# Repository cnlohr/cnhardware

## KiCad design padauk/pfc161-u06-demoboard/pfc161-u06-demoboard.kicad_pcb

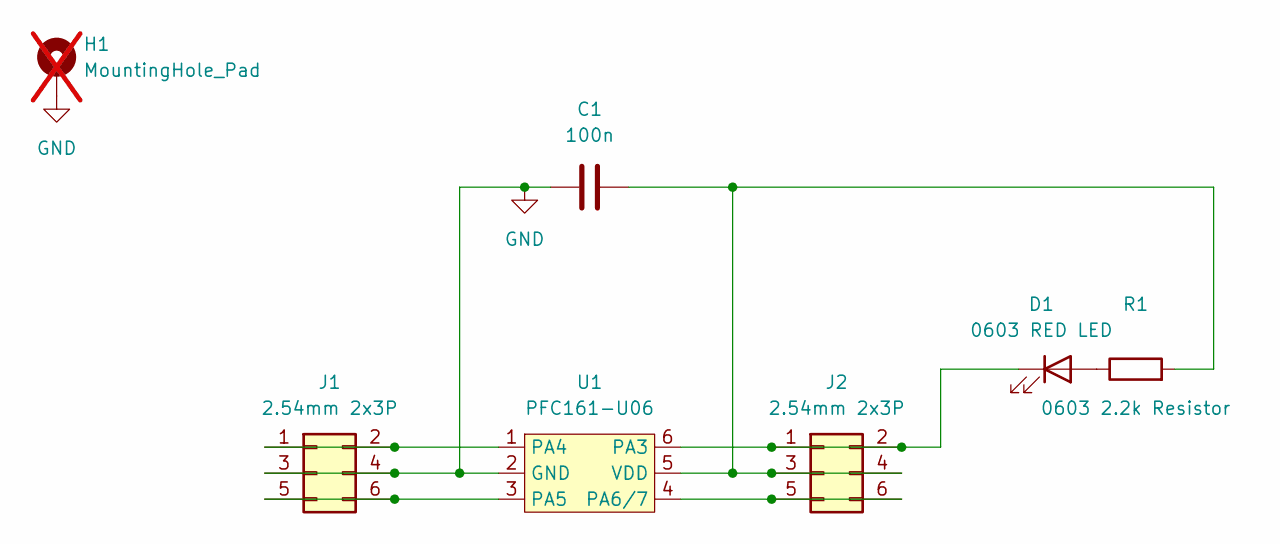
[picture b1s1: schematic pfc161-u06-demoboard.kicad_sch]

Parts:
C1: 100n; C_0402_1005Metric; LCSC C1525
D1: 0603 RED LED; LED_0603_1608Metric; LCSC C2286
H1: MountingHole_Pad; MountingHole_3.2mm_M3_Pad; not fitted
J1, J2: 2.54mm 2x3P; PinHeader_2x03_P2.54mm_Vertical; LCSC C65114
R1: 0603 2.2k Resistor; R_0603_1608Metric; LCSC C2907137
U1: PFC161-U06; SOT-23-6; LCSC C2909526

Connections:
GND: C1.1, H1.1, J1.3, J1.4, U1.2 (GND)
unnamed: D1.2 (A), R1.1
unnamed: D1.1 (K), J2.1, J2.2, U1.6 (PA3)
unnamed: J1.1, J1.2, U1.1 (PA4)
unnamed: J1.5, J1.6, U1.3 (PA5)
unnamed: C1.2, J2.3, J2.4, R1.2, U1.5 (VDD)
unnamed: J2.5, J2.6, U1.4 (PA6/7)

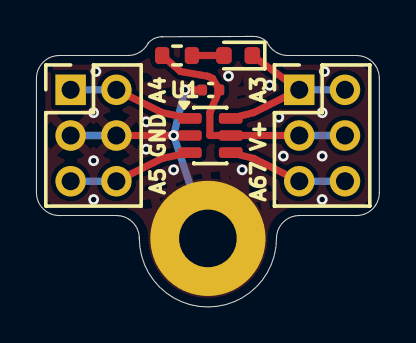
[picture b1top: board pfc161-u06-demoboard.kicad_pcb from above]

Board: 2 copper layers, 19.0 x 15.0 mm, 7 parts (0 on the bottom side), 7 nets.

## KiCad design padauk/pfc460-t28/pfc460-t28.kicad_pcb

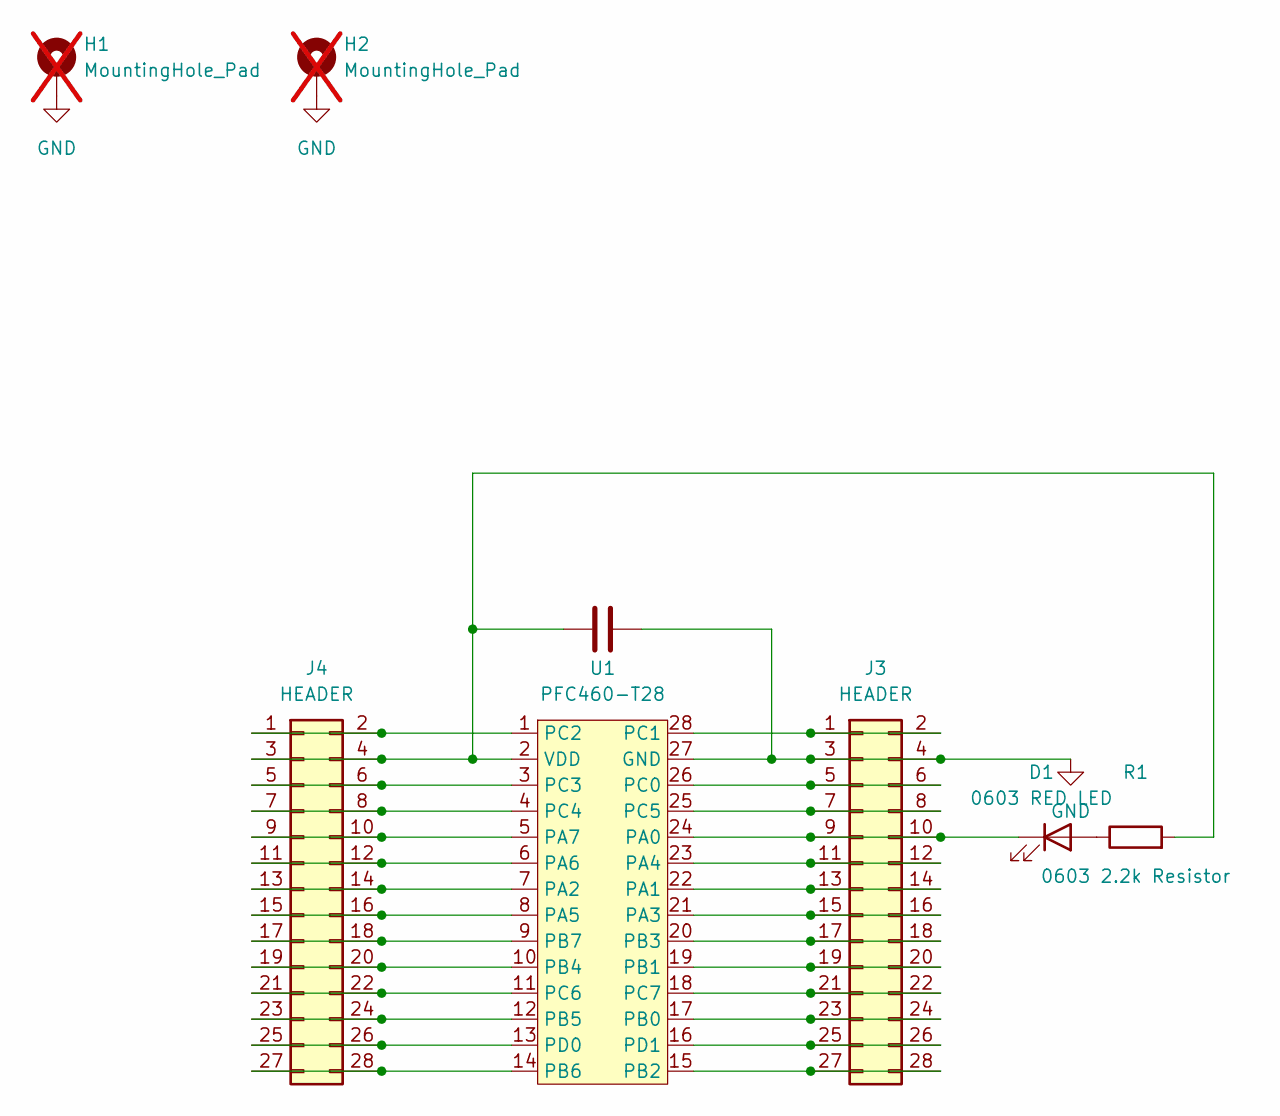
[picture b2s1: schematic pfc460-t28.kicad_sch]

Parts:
C2: 100n; C_0402_1005Metric; LCSC C1525
D1: 0603 RED LED; LED_0603_1608Metric; LCSC C2286
H1, H2: MountingHole_Pad; MountingHole_3.2mm_M3_Pad; not fitted
J3, J4: HEADER; PinHeader_2x14_P2.54mm_Vertical; LCSC C41376105
R1: 0603 2.2k Resistor; R_0603_1608Metric; LCSC C2907137
U1: PFC460-T28; TSSOP-28_4.4x9.7mm_P0.65mm; LCSC C22365215

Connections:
GND: C2.2, H1.1, H2.1, J3.3, J3.4, U1.27 (GND)
unnamed: D1.2 (A), R1.1
unnamed: D1.1 (K), J3.9, J3.10, U1.24 (PA0)
unnamed: J3.1, J3.2, U1.28 (PC1)
unnamed: J3.5, J3.6, U1.26 (PC0)
unnamed: J3.7, J3.8, U1.25 (PC5)
unnamed: J3.11, J3.12, U1.23 (PA4)
unnamed: J3.13, J3.14, U1.22 (PA1)
unnamed: J3.15, J3.16, U1.21 (PA3)
unnamed: J3.17, J3.18, U1.20 (PB3)
unnamed: J3.19, J3.20, U1.19 (PB1)
unnamed: J3.21, J3.22, U1.18 (PC7)
unnamed: J3.23, J3.24, U1.17 (PB0)
unnamed: J3.25, J3.26, U1.16 (PD1)
unnamed: J3.27, J3.28, U1.15 (PB2)
unnamed: J4.1, J4.2, U1.1 (PC2)
unnamed: C2.1, J4.3, J4.4, R1.2, U1.2 (VDD)
unnamed: J4.5, J4.6, U1.3 (PC3)
unnamed: J4.7, J4.8, U1.4 (PC4)
unnamed: J4.9, J4.10, U1.5 (PA7)
unnamed: J4.11, J4.12, U1.6 (PA6)
unnamed: J4.13, J4.14, U1.7 (PA2)
unnamed: J4.15, J4.16, U1.8 (PA5)
unnamed: J4.17, J4.18, U1.9 (PB7)
unnamed: J4.19, J4.20, U1.10 (PB4)
unnamed: J4.21, J4.22, U1.11 (PC6)
unnamed: J4.23, J4.24, U1.12 (PB5)
unnamed: J4.25, J4.26, U1.13 (PD0)
unnamed: J4.27, J4.28, U1.14 (PB6)

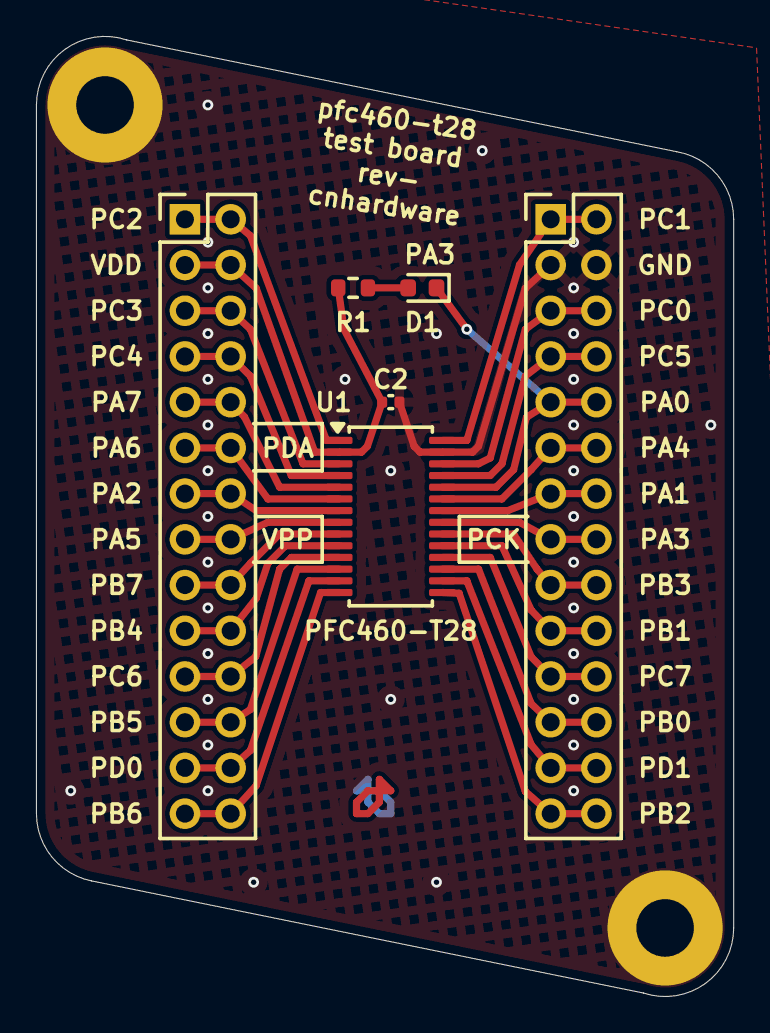
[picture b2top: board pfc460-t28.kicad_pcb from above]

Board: 2 copper layers, 38.7 x 53.3 mm, 8 parts (0 on the bottom side), 29 nets.

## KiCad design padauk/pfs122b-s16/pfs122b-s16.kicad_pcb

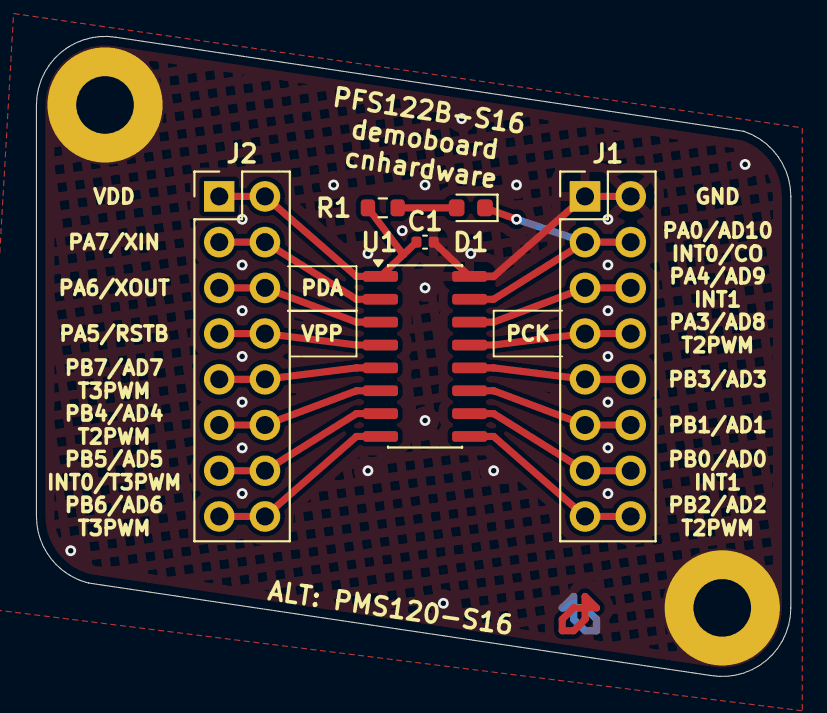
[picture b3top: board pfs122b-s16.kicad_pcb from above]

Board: 2 copper layers, 41.9 x 35.6 mm, 8 parts (0 on the bottom side), 17 nets.

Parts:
C1: 100n; C_0402_1005Metric
D1: LED; LED_0603_1608Metric
H1, H2: MountingHole_Pad; MountingHole_3.2mm_M3_Pad
J1, J2: 2.54mm Header 2x08P; PinHeader_2x08_P2.54mm_Vertical
R1: R; R_0603_1608Metric
U1: PFS122B-S16; SOIC-16_3.9x9.9mm_P1.27mm

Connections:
GND: C1.2, H1.1, H2.1, J1.1, J1.2, U1.16 (GND)
unnamed: D1.2 (A), R1.1
unnamed: D1.1 (K), J1.3, J1.4, U1.15 (PA0)
unnamed: J1.5, J1.6, U1.14 (PA4)
unnamed: J1.7, J1.8, U1.13 (PA3)
unnamed: J1.9, J1.10, U1.12 (PB3)
unnamed: J1.11, J1.12, U1.11 (PB1)
unnamed: J1.13, J1.14, U1.10 (PB0)
unnamed: J1.15, J1.16, U1.9 (PB2)
unnamed: C1.1, J2.1, J2.2, R1.2, U1.1 (VDD)
unnamed: J2.3, J2.4, U1.2 (PA7)
unnamed: J2.5, J2.6, U1.3 (PA6)
unnamed: J2.7, J2.8, U1.4 (PA5)
unnamed: J2.9, J2.10, U1.5 (PB7)
unnamed: J2.11, J2.12, U1.6 (PB4)
unnamed: J2.13, J2.14, U1.7 (PB5)
unnamed: J2.15, J2.16, U1.8 (PB6)

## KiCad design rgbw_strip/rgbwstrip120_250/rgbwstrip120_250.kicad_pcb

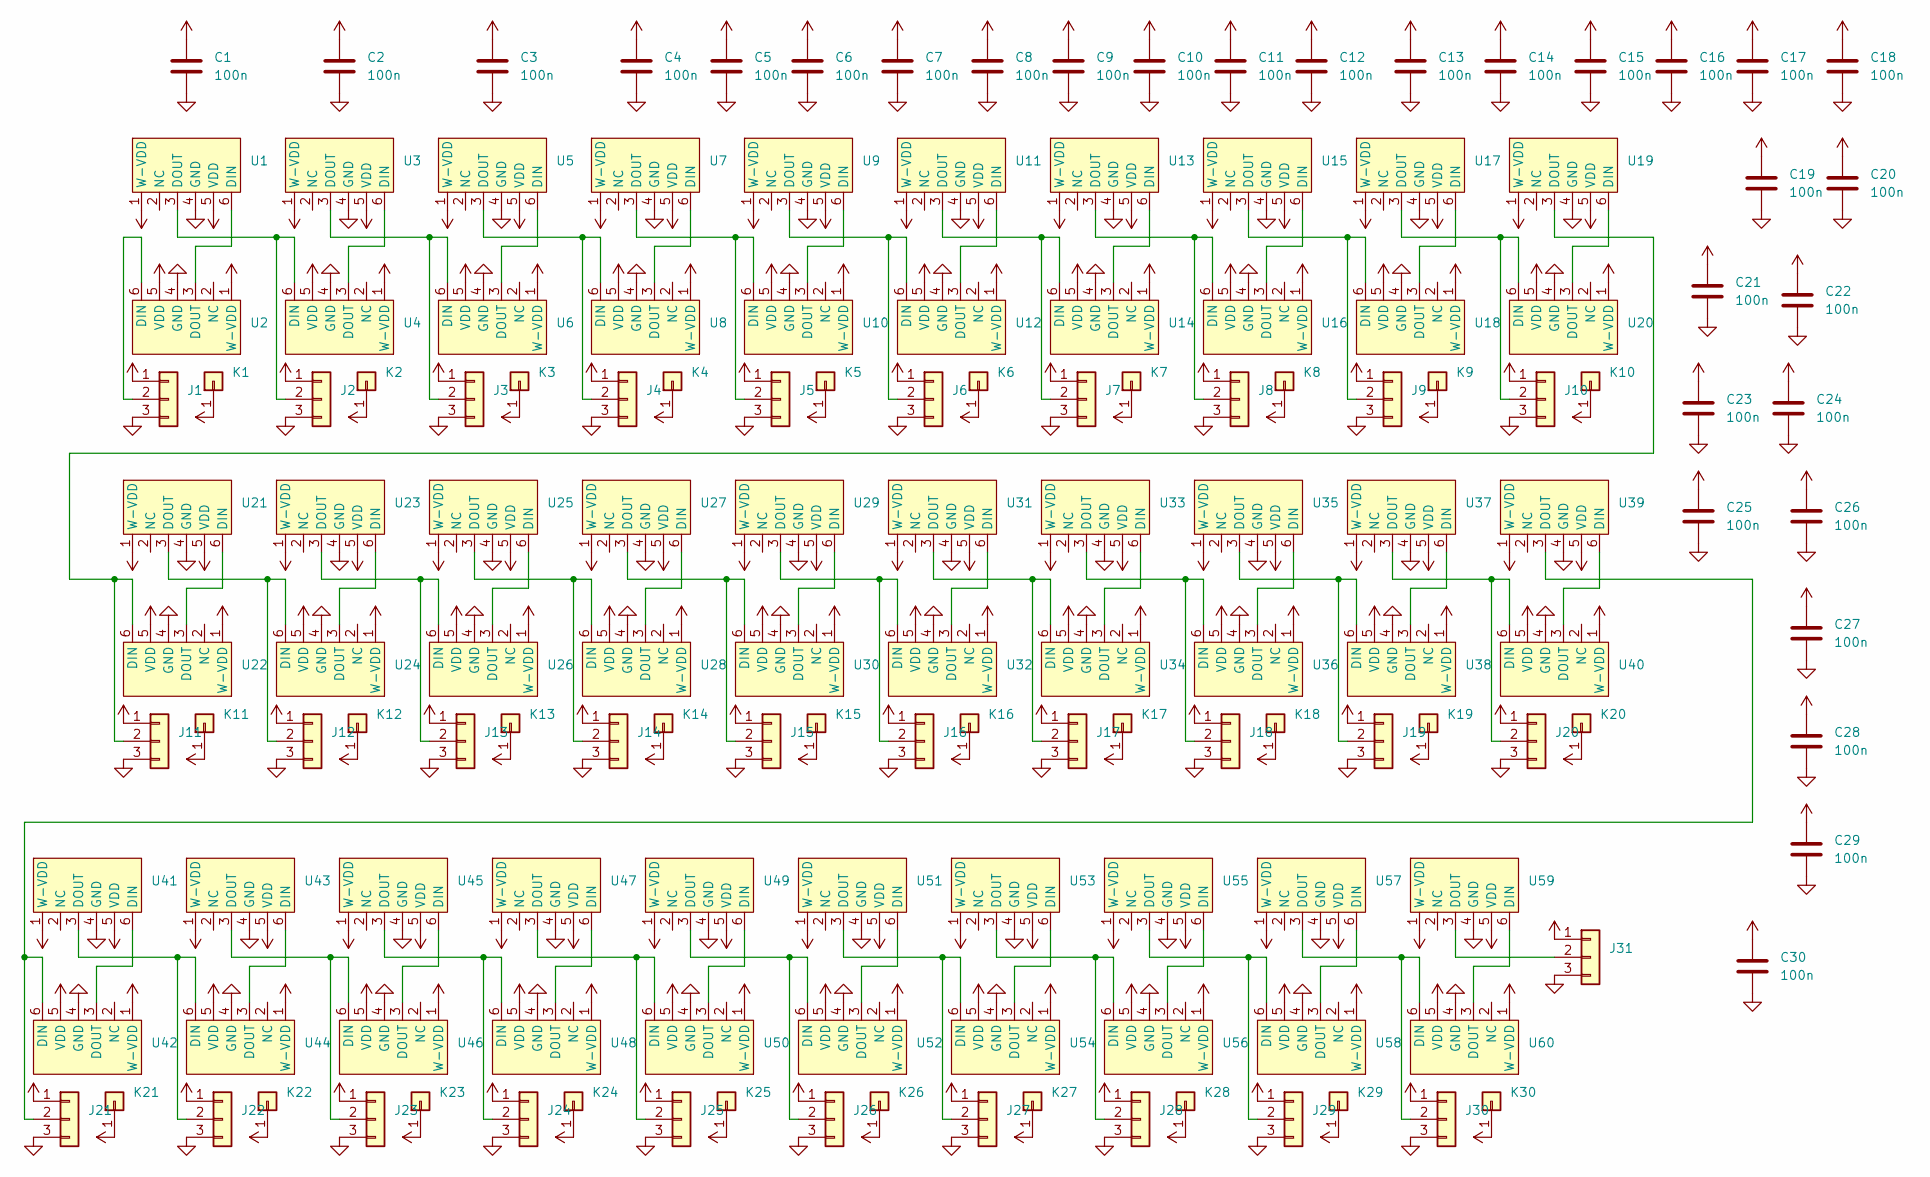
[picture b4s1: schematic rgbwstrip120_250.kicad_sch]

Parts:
C1, C2, C3, C4, C5, C6, C7, C8, C9, C10, C11, C12, C13, C14, C15, C16, C17, C18, C19, C20, C21, C22, C23, C24, C25, C26, C27, C28, C29, C30: 100n; C_0402_1005Metric; LCSC C1525
J1, J2, J3, J4, J5, J6, J7, J8, J9, J10, J11, J12, J13, J14, J15, J16, J17, J18, J19, J20, J21, J22, J23, J24, J25, J26, J27, J28, J29, J30, J31: 3PADSPLIT
K1, K2, K3, K4, K5, K6, K7, K8, K9, K10, K11, K12, K13, K14, K15, K16, K17, K18, K19, K20, K21, K22, K23, K24, K25, K26, K27, K28, K29, K30: Conn_01x01; PINPAD
U1, U2, U3, U4, U5, U6, U7, U8, U9, U10, U11, U12, U13, U14, U15, U16, U17, U18, U19, U20, U21, U22, U23, U24, U25, U26, U27, U28, U29, U30, U31, U32, U33, U34, U35, U36, U37, U38, U39, U40, U41, U42, U43, U44, U45, U46, U47, U48, U49, U50, U51, U52, U53, U54, U55, U56, U57, U58, U59, U60: SK6805SIDE-FRGBW-BW-P6; LCSC C7423108

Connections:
+3.3V: C1.1, C2.1, C3.1, C4.1, C5.1, C6.1, C7.1, C8.1, C9.1, C10.1, C11.1, C12.1, C13.1, C14.1, C15.1, C16.1, C17.1, C18.1, C19.1, C20.1, C21.1, C22.1, C23.1, C24.1, C25.1, C26.1, C27.1, C28.1, C29.1, C30.1, J1.1, J2.1, J3.1, J4.1, J5.1, J6.1, J7.1, J8.1, J9.1, J10.1, J11.1, J12.1, J13.1, J14.1, J15.1, J16.1, J17.1, J18.1, J19.1, J20.1, J21.1, J22.1, J23.1, J24.1, J25.1, J26.1, J27.1, J28.1, J29.1, J30.1, J31.1, K1.1, K2.1, K3.1, K4.1, K5.1, K6.1, K7.1, K8.1, K9.1, K10.1, K11.1, K12.1, K13.1, K14.1, K15.1, K16.1, K17.1, K18.1, K19.1, K20.1, K21.1, K22.1, K23.1, K24.1, K25.1, K26.1, K27.1, K28.1, K29.1, K30.1, U1.1 (W-VDD), U1.5 (VDD), U2.1 (W-VDD), U2.5 (VDD), U3.1 (W-VDD), U3.5 (VDD), U4.1 (W-VDD), U4.5 (VDD), U5.1 (W-VDD), U5.5 (VDD), U6.1 (W-VDD), U6.5 (VDD), U7.1 (W-VDD), U7.5 (VDD), U8.1 (W-VDD), U8.5 (VDD), U9.1 (W-VDD), U9.5 (VDD), U10.1 (W-VDD), U10.5 (VDD), U11.1 (W-VDD), U11.5 (VDD), U12.1 (W-VDD), U12.5 (VDD), U13.1 (W-VDD), U13.5 (VDD), U14.1 (W-VDD), U14.5 (VDD), U15.1 (W-VDD), U15.5 (VDD), U16.1 (W-VDD), U16.5 (VDD), U17.1 (W-VDD), U17.5 (VDD), U18.1 (W-VDD), U18.5 (VDD), U19.1 (W-VDD), U19.5 (VDD), U20.1 (W-VDD), U20.5 (VDD), U21.1 (W-VDD), U21.5 (VDD), U22.1 (W-VDD), U22.5 (VDD), U23.1 (W-VDD), U23.5 (VDD), U24.1 (W-VDD), U24.5 (VDD), U25.1 (W-VDD), U25.5 (VDD), U26.1 (W-VDD), U26.5 (VDD), U27.1 (W-VDD), U27.5 (VDD), U28.1 (W-VDD), U28.5 (VDD), U29.1 (W-VDD), U29.5 (VDD), U30.1 (W-VDD), U30.5 (VDD), U31.1 (W-VDD), U31.5 (VDD), U32.1 (W-VDD), U32.5 (VDD), U33.1 (W-VDD), U33.5 (VDD), U34.1 (W-VDD), U34.5 (VDD), U35.1 (W-VDD), U35.5 (VDD), U36.1 (W-VDD), U36.5 (VDD), U37.1 (W-VDD), U37.5 (VDD), U38.1 (W-VDD), U38.5 (VDD), U39.1 (W-VDD), U39.5 (VDD), U40.1 (W-VDD), U40.5 (VDD), U41.1 (W-VDD), U41.5 (VDD), U42.1 (W-VDD), U42.5 (VDD), U43.1 (W-VDD), U43.5 (VDD), U44.1 (W-VDD), U44.5 (VDD), U45.1 (W-VDD), U45.5 (VDD), U46.1 (W-VDD), U46.5 (VDD), U47.1 (W-VDD), U47.5 (VDD), U48.1 (W-VDD), U48.5 (VDD), U49.1 (W-VDD), U49.5 (VDD), U50.1 (W-VDD), U50.5 (VDD), U51.1 (W-VDD), U51.5 (VDD), U52.1 (W-VDD), U52.5 (VDD), U53.1 (W-VDD), U53.5 (VDD), U54.1 (W-VDD), U54.5 (VDD), U55.1 (W-VDD), U55.5 (VDD), U56.1 (W-VDD), U56.5 (VDD), U57.1 (W-VDD), U57.5 (VDD), U58.1 (W-VDD), U58.5 (VDD), U59.1 (W-VDD), U59.5 (VDD), U60.1 (W-VDD), U60.5 (VDD)
GND: C1.2, C2.2, C3.2, C4.2, C5.2, C6.2, C7.2, C8.2, C9.2, C10.2, C11.2, C12.2, C13.2, C14.2, C15.2, C16.2, C17.2, C18.2, C19.2, C20.2, C21.2, C22.2, C23.2, C24.2, C25.2, C26.2, C27.2, C28.2, C29.2, C30.2, J1.3, J2.3, J3.3, J4.3, J5.3, J6.3, J7.3, J8.3, J9.3, J10.3, J11.3, J12.3, J13.3, J14.3, J15.3, J16.3, J17.3, J18.3, J19.3, J20.3, J21.3, J22.3, J23.3, J24.3, J25.3, J26.3, J27.3, J28.3, J29.3, J30.3, J31.3, U1.4 (GND), U2.4 (GND), U3.4 (GND), U4.4 (GND), U5.4 (GND), U6.4 (GND), U7.4 (GND), U8.4 (GND), U9.4 (GND), U10.4 (GND), U11.4 (GND), U12.4 (GND), U13.4 (GND), U14.4 (GND), U15.4 (GND), U16.4 (GND), U17.4 (GND), U18.4 (GND), U19.4 (GND), U20.4 (GND), U21.4 (GND), U22.4 (GND), U23.4 (GND), U24.4 (GND), U25.4 (GND), U26.4 (GND), U27.4 (GND), U28.4 (GND), U29.4 (GND), U30.4 (GND), U31.4 (GND), U32.4 (GND), U33.4 (GND), U34.4 (GND), U35.4 (GND), U36.4 (GND), U37.4 (GND), U38.4 (GND), U39.4 (GND), U40.4 (GND), U41.4 (GND), U42.4 (GND), U43.4 (GND), U44.4 (GND), U45.4 (GND), U46.4 (GND), U47.4 (GND), U48.4 (GND), U49.4 (GND), U50.4 (GND), U51.4 (GND), U52.4 (GND), U53.4 (GND), U54.4 (GND), U55.4 (GND), U56.4 (GND), U57.4 (GND), U58.4 (GND), U59.4 (GND), U60.4 (GND)
unnamed: J1.2, U2.6 (DIN)
unnamed: J2.2, U1.3 (DOUT), U4.6 (DIN)
unnamed: J3.2, U3.3 (DOUT), U6.6 (DIN)
unnamed: J4.2, U5.3 (DOUT), U8.6 (DIN)
unnamed: J5.2, U7.3 (DOUT), U10.6 (DIN)
unnamed: J6.2, U9.3 (DOUT), U12.6 (DIN)
unnamed: J7.2, U11.3 (DOUT), U14.6 (DIN)
unnamed: J8.2, U13.3 (DOUT), U16.6 (DIN)
unnamed: J9.2, U15.3 (DOUT), U18.6 (DIN)
unnamed: J10.2, U17.3 (DOUT), U20.6 (DIN)
unnamed: J11.2, U19.3 (DOUT), U22.6 (DIN)
unnamed: J12.2, U21.3 (DOUT), U24.6 (DIN)
unnamed: J13.2, U23.3 (DOUT), U26.6 (DIN)
unnamed: J14.2, U25.3 (DOUT), U28.6 (DIN)
unnamed: J15.2, U27.3 (DOUT), U30.6 (DIN)
unnamed: J16.2, U29.3 (DOUT), U32.6 (DIN)
unnamed: J17.2, U31.3 (DOUT), U34.6 (DIN)
unnamed: J18.2, U33.3 (DOUT), U36.6 (DIN)
unnamed: J19.2, U35.3 (DOUT), U38.6 (DIN)
unnamed: J20.2, U37.3 (DOUT), U40.6 (DIN)
unnamed: J21.2, U39.3 (DOUT), U42.6 (DIN)
unnamed: J22.2, U41.3 (DOUT), U44.6 (DIN)
unnamed: J23.2, U43.3 (DOUT), U46.6 (DIN)
unnamed: J24.2, U45.3 (DOUT), U48.6 (DIN)
unnamed: J25.2, U47.3 (DOUT), U50.6 (DIN)
unnamed: J26.2, U49.3 (DOUT), U52.6 (DIN)
unnamed: J27.2, U51.3 (DOUT), U54.6 (DIN)
unnamed: J28.2, U53.3 (DOUT), U56.6 (DIN)
unnamed: J29.2, U55.3 (DOUT), U58.6 (DIN)
unnamed: J30.2, U57.3 (DOUT), U60.6 (DIN)
unnamed: J31.2, U59.3 (DOUT)
unnamed: U1.6 (DIN), U2.3 (DOUT)
unnamed: U3.6 (DIN), U4.3 (DOUT)
unnamed: U5.6 (DIN), U6.3 (DOUT)
unnamed: U7.6 (DIN), U8.3 (DOUT)
unnamed: U9.6 (DIN), U10.3 (DOUT)
unnamed: U11.6 (DIN), U12.3 (DOUT)
unnamed: U13.6 (DIN), U14.3 (DOUT)
unnamed: U15.6 (DIN), U16.3 (DOUT)
unnamed: U17.6 (DIN), U18.3 (DOUT)
unnamed: U19.6 (DIN), U20.3 (DOUT)
unnamed: U21.6 (DIN), U22.3 (DOUT)
unnamed: U23.6 (DIN), U24.3 (DOUT)
unnamed: U25.6 (DIN), U26.3 (DOUT)
unnamed: U27.6 (DIN), U28.3 (DOUT)
unnamed: U29.6 (DIN), U30.3 (DOUT)
unnamed: U31.6 (DIN), U32.3 (DOUT)
unnamed: U33.6 (DIN), U34.3 (DOUT)
unnamed: U35.6 (DIN), U36.3 (DOUT)
unnamed: U37.6 (DIN), U38.3 (DOUT)
unnamed: U39.6 (DIN), U40.3 (DOUT)
unnamed: U41.6 (DIN), U42.3 (DOUT)
unnamed: U43.6 (DIN), U44.3 (DOUT)
unnamed: U45.6 (DIN), U46.3 (DOUT)
unnamed: U47.6 (DIN), U48.3 (DOUT)
unnamed: U49.6 (DIN), U50.3 (DOUT)
unnamed: U51.6 (DIN), U52.3 (DOUT)
unnamed: U53.6 (DIN), U54.3 (DOUT)
unnamed: U55.6 (DIN), U56.3 (DOUT)
unnamed: U57.6 (DIN), U58.3 (DOUT)
unnamed: U59.6 (DIN), U60.3 (DOUT)

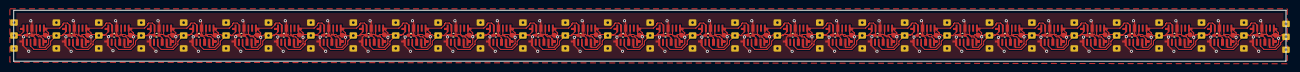
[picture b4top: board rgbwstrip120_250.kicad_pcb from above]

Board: 2 copper layers, 250.0 x 10.0 mm, 151 parts (0 on the bottom side), 63 nets.

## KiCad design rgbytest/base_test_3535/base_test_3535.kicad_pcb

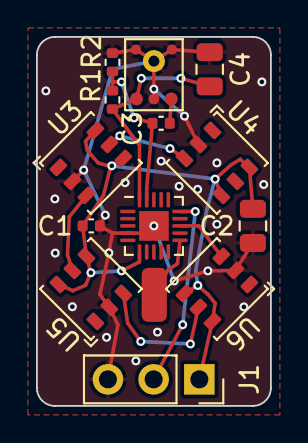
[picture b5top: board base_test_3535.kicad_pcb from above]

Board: 2 copper layers, 13.0 x 20.5 mm, 14 parts (0 on the bottom side), 11 nets.

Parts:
C1, C3: 1u; C_0402_1005Metric
C2, C4: 22uF; C_0805_2012Metric
J1: PGM; PinSocket_1x03_P2.54mm_Vertical
J2: touchpad_10x6.5mm_retircle
R1: 243k; R_0402_1005Metric
R2: 100k; R_0402_1005Metric
U1: CH32V003F4U6; QFN-20-1EP_3x3mm_P0.4mm_EP1.65x1.65mm
U2: S08OB383-031; GOERTEK-S08OB383-031-MemsMic
U3, U4, U5, U6: LC8812BC-3535RGBY

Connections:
A2: J2.1, U1.11 (PC4/A2/T1CH4/MCO/T1CH1CH2N)
GND: C1.2, C2.2, C4.2, J1.3, R2.2, U1.4 (VSS), U1.21 (GND), U2.2 (GND), U2.3 (GND), U2.5 (GND), U2.6 (GND), U3.2 (GND), U4.2 (GND), U5.2 (GND), U6.2 (GND)
unnamed: C3.1, U2.1 (OUT)
unnamed: U3.3 (DIN), U5.5 (DOUT)
unnamed: U3.5 (DOUT), U4.3 (DIN)
unnamed: U5.3 (DIN), U6.5 (DOUT)
PD6: C4.1, R1.2, U1.20 (PD6/A7/URX/T2CH3/UTX), U2.4 (PWR)
SWIO: J1.2, U1.15 (PD1/SWIO/AETR/T1CH3/SCL/URX)
VCCMON: C3.2, R1.1, R2.1, U1.19 (PD5/A5/UTX/T2CH4/URX)
VDD: C1.1, C2.1, J1.1, U1.6 (VDD), U3.4 (VDD), U3.6 (VDD), U4.4 (VDD), U4.6 (VDD), U5.4 (VDD), U5.6 (VDD), U6.4 (VDD), U6.6 (VDD)
WS2812B: U1.13 (PC6/MOSI/T1CH1CH3/UCTS/SDA), U6.3 (DIN)

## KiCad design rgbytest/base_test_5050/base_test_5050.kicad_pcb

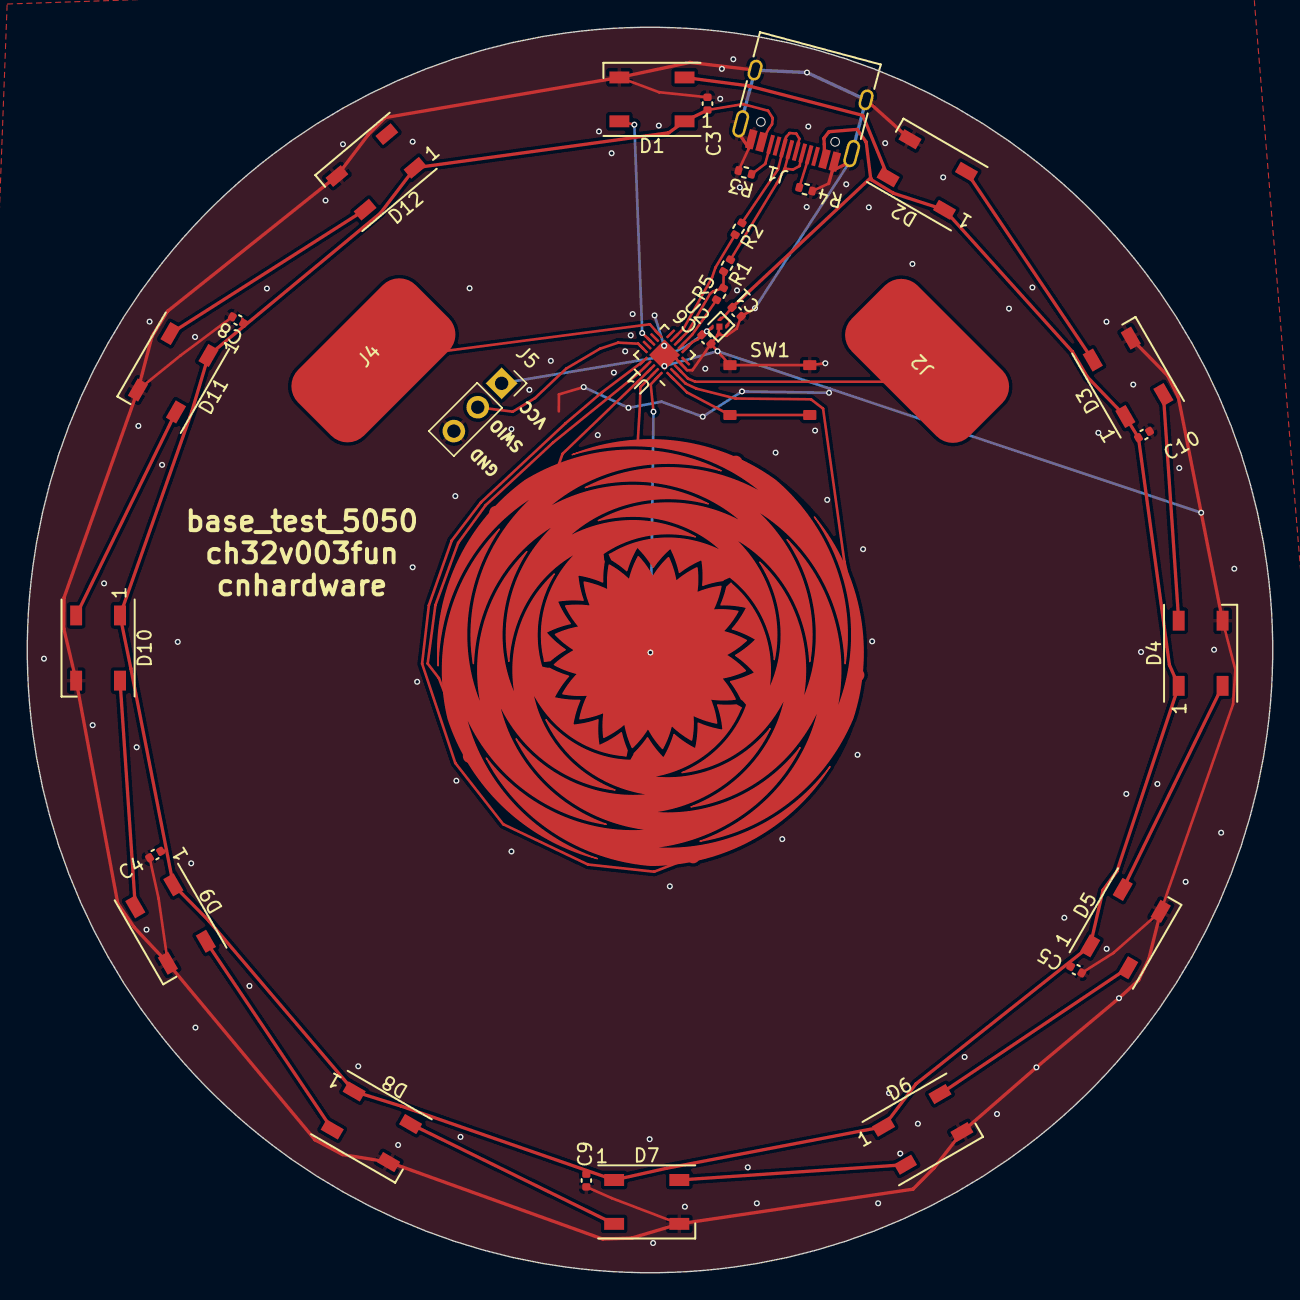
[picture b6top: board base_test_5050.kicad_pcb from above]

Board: 2 copper layers, 93.6 x 93.6 mm, 33 parts (0 on the bottom side), 32 nets.

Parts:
C1, C3, C4, C5, C6, C8, C9, C10: 1u; C_0402_1005Metric
D1, D2, D3, D4, D5, D6, D7, D8, D9, D10, D11, D12: LC8812B-5050RGBY; LED_WS2812B_PLCC4_5.0x5.0mm_P3.2mm
J1: USB_C_Receptacle_USB2.0; USB_C_Receptacle_HRO_TYPE-C-31-M-12
J2, J4: touchpad_12.5x7mm_retircle
J3: TouchTeeth; Touch_Teeth_5
J5: PGM; PinSocket_1x03_P2.54mm_Vertical
R1, R2: 33; R_0402_1005Metric
R3, R4: 5.1k; R_0402_1005Metric
R5: 1.5k 1%; R_0402_1005Metric
SW1: BOOT; TS-1187A-B-A-B-TACTILE
U1: CH32V003F4U6; QFN-20-1EP_3x3mm_P0.4mm_EP1.65x1.65mm
U2: 3.3vReg; xdfn-reg

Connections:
+5V: C1.1, C3.1, C4.1, C5.1, C8.1, C9.1, C10.1, D1.1 (VDD), D2.1 (VDD), D3.1 (VDD), D4.1 (VDD), D5.1 (VDD), D6.1 (VDD), D7.1 (VDD), D8.1 (VDD), D9.1 (VDD), D10.1 (VDD), D11.1 (VDD), D12.1 (VDD), J1.A4 (VBUS), J1.A9 (VBUS), J1.B4 (VBUS), J1.B9 (VBUS), U2.3 (EN), U2.4 (IN)
A0: J2.1, U1.3 (PA2/OSCO/A0/T1CH2N/OPP0/AETR2)
A1: J3.4, U1.2 (PA1/OSCI/A1/T1CH2/OPN0)
A2: J4.1, U1.11 (PC4/A2/T1CH4/MCO/T1CH1CH2N)
A3: J3.6, U1.16 (PD2/A3/T1CH1/T2CH3/T1CH2N)
A4: J3.5, U1.17 (PD3/A4/T2CH2/AETR/UCTS/T1CH4)
A5: J3.1, U1.19 (PD5/A5/UTX/T2CH4/URX)
A6: J3.3, U1.20 (PD6/A7/URX/T2CH3/UTX)
A7: J3.2, U1.18 (PD4/A7/UCK/T2CH1ETR/OPO/T1CH4ETR)
D+: R2.2, U1.9 (PC2/SCL/URTS/T1BKIN/AETR/T2CH2/T1ETR)
D-: R1.2, R5.1, U1.8 (PC1/SDA/NSS/T2CH4/T2CH1ETR/T1BKIN/URX)
DPU: R5.2, U1.7 (PC0/T2CH3/UTX/NSS/T1CH3)
GND: C1.2, C3.2, C4.2, C5.2, C6.2, C8.2, C9.2, C10.2, D1.3 (VSS), D2.3 (VSS), D3.3 (VSS), D4.3 (VSS), D5.3 (VSS), D6.3 (VSS), D7.3 (VSS), D8.3 (VSS), D9.3 (VSS), D10.3 (VSS), D11.3 (VSS), D12.3 (VSS), J1.A1 (GND), J1.A12 (GND), J1.B1 (GND), J1.B12 (GND), J1.S1 (SHIELD), J5.3, R3.2, R4.2, SW1.1 (A), U1.4 (VSS), U1.21 (GND), U2.2 (GND), U2.5 (GND)
unnamed: D1.2 (DOUT), D2.4 (DIN)
unnamed: D2.2 (DOUT), D3.4 (DIN)
unnamed: D3.2 (DOUT), D4.4 (DIN)
unnamed: D4.2 (DOUT), D5.4 (DIN)
unnamed: D5.2 (DOUT), D6.4 (DIN)
unnamed: D6.2 (DOUT), D7.4 (DIN)
unnamed: D7.2 (DOUT), D8.4 (DIN)
unnamed: D8.2 (DOUT), D9.4 (DIN)
unnamed: D9.2 (DOUT), D10.4 (DIN)
unnamed: D10.2 (DOUT), D11.4 (DIN)
unnamed: D11.2 (DOUT), D12.4 (DIN)
unnamed: J1.A5 (CC1), R4.1
unnamed: J1.B5 (CC2), R3.1
unnamed: J1.A6 (D+), J1.B6 (D+), R2.1
unnamed: J1.A7 (D-), J1.B7 (D-), R1.1
PD7NRST: SW1.2 (B), U1.1 (PD7/NRST/T2CH4/OPP1/UCK)
SWIO: J5.2, U1.15 (PD1/SWIO/AETR/T1CH3/SCL/URX)
VDD: C6.1, J5.1, U1.6 (VDD), U2.1 (OUT)
WS2812B: D1.4 (DIN), U1.13 (PC6/MOSI/T1CH1CH3/UCTS/SDA)

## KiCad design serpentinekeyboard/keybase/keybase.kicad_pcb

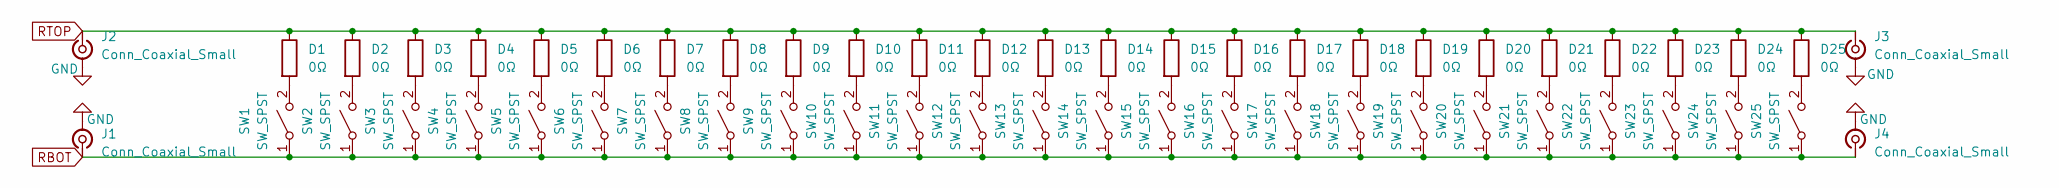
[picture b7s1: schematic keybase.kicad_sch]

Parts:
D1, D2, D3, D4, D5, D6, D7, D8, D9, D10, D11, D12, D13, D14, D15, D16, D17, D18, D19, D20, D21, D22, D23, D24, D25: 0Ω; KeyboardManualSolder_0805
J1, J2, J3, J4: Conn_Coaxial_Small; SMA_Samtec_SMA-J-P-H-ST-EM1_EdgeMount
SW1, SW2, SW3, SW4, SW5, SW6, SW7, SW8, SW9, SW10, SW11, SW12, SW13, SW14, SW15, SW16, SW17, SW18, SW19, SW20, SW21, SW22, SW23, SW24, SW25: SW_SPST; SW_Cherry_MX_1.00u_PCB_NO_MOUNTING; LCSC C404353

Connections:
GND: J1.2 (Ext), J2.2 (Ext), J3.2 (Ext), J4.2 (Ext)
unnamed: D1.2, SW1.2 (B)
unnamed: D2.2, SW2.2 (B)
unnamed: D3.2, SW3.2 (B)
unnamed: D4.2, SW4.2 (B)
unnamed: D5.2, SW5.2 (B)
unnamed: D6.2, SW6.2 (B)
unnamed: D7.2, SW7.2 (B)
unnamed: D8.2, SW8.2 (B)
unnamed: D9.2, SW9.2 (B)
unnamed: D10.2, SW10.2 (B)
unnamed: D11.2, SW11.2 (B)
unnamed: D12.2, SW12.2 (B)
unnamed: D13.2, SW13.2 (B)
unnamed: D14.2, SW14.2 (B)
unnamed: D15.2, SW15.2 (B)
unnamed: D16.2, SW16.2 (B)
unnamed: D17.2, SW17.2 (B)
unnamed: D18.2, SW18.2 (B)
unnamed: D19.2, SW19.2 (B)
unnamed: D20.2, SW20.2 (B)
unnamed: D21.2, SW21.2 (B)
unnamed: D22.2, SW22.2 (B)
unnamed: D23.2, SW23.2 (B)
unnamed: D24.2, SW24.2 (B)
unnamed: D25.2, SW25.2 (B)
RBOT: J1.1 (In), J4.1 (In), SW1.1 (A), SW2.1 (A), SW3.1 (A), SW4.1 (A), SW5.1 (A), SW6.1 (A), SW7.1 (A), SW8.1 (A), SW9.1 (A), SW10.1 (A), SW11.1 (A), SW12.1 (A), SW13.1 (A), SW14.1 (A), SW15.1 (A), SW16.1 (A), SW17.1 (A), SW18.1 (A), SW19.1 (A), SW20.1 (A), SW21.1 (A), SW22.1 (A), SW23.1 (A), SW24.1 (A), SW25.1 (A)
RTOP: D1.1, D2.1, D3.1, D4.1, D5.1, D6.1, D7.1, D8.1, D9.1, D10.1, D11.1, D12.1, D13.1, D14.1, D15.1, D16.1, D17.1, D18.1, D19.1, D20.1, D21.1, D22.1, D23.1, D24.1, D25.1, J2.1 (In), J3.1 (In)

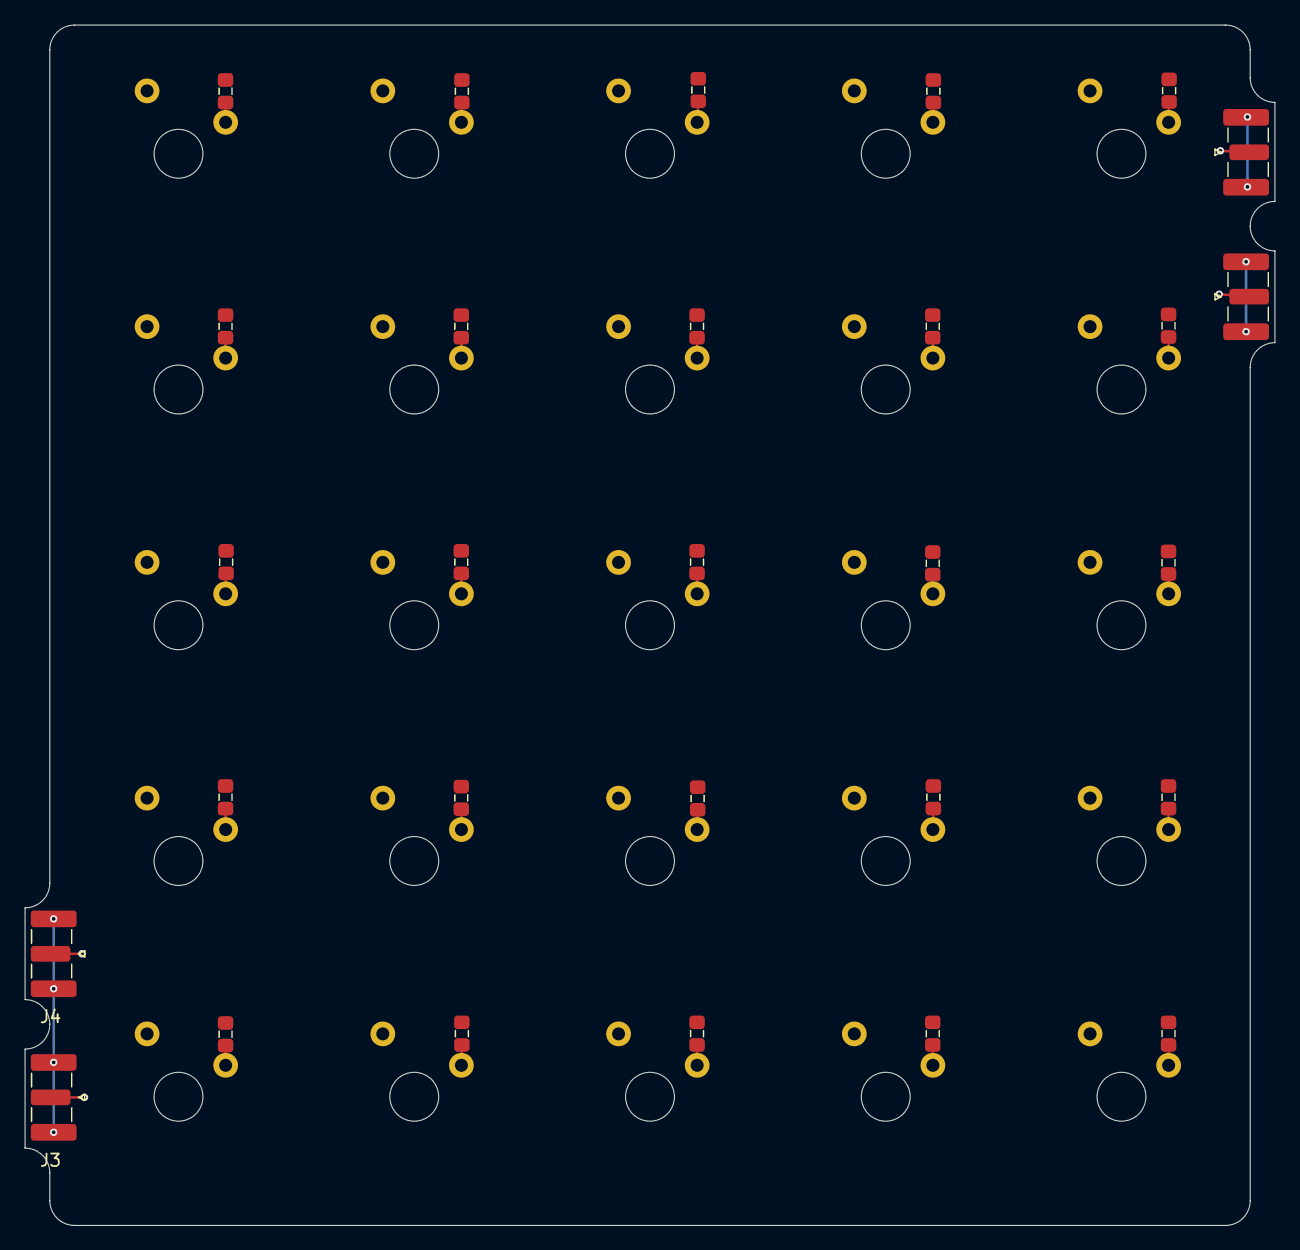
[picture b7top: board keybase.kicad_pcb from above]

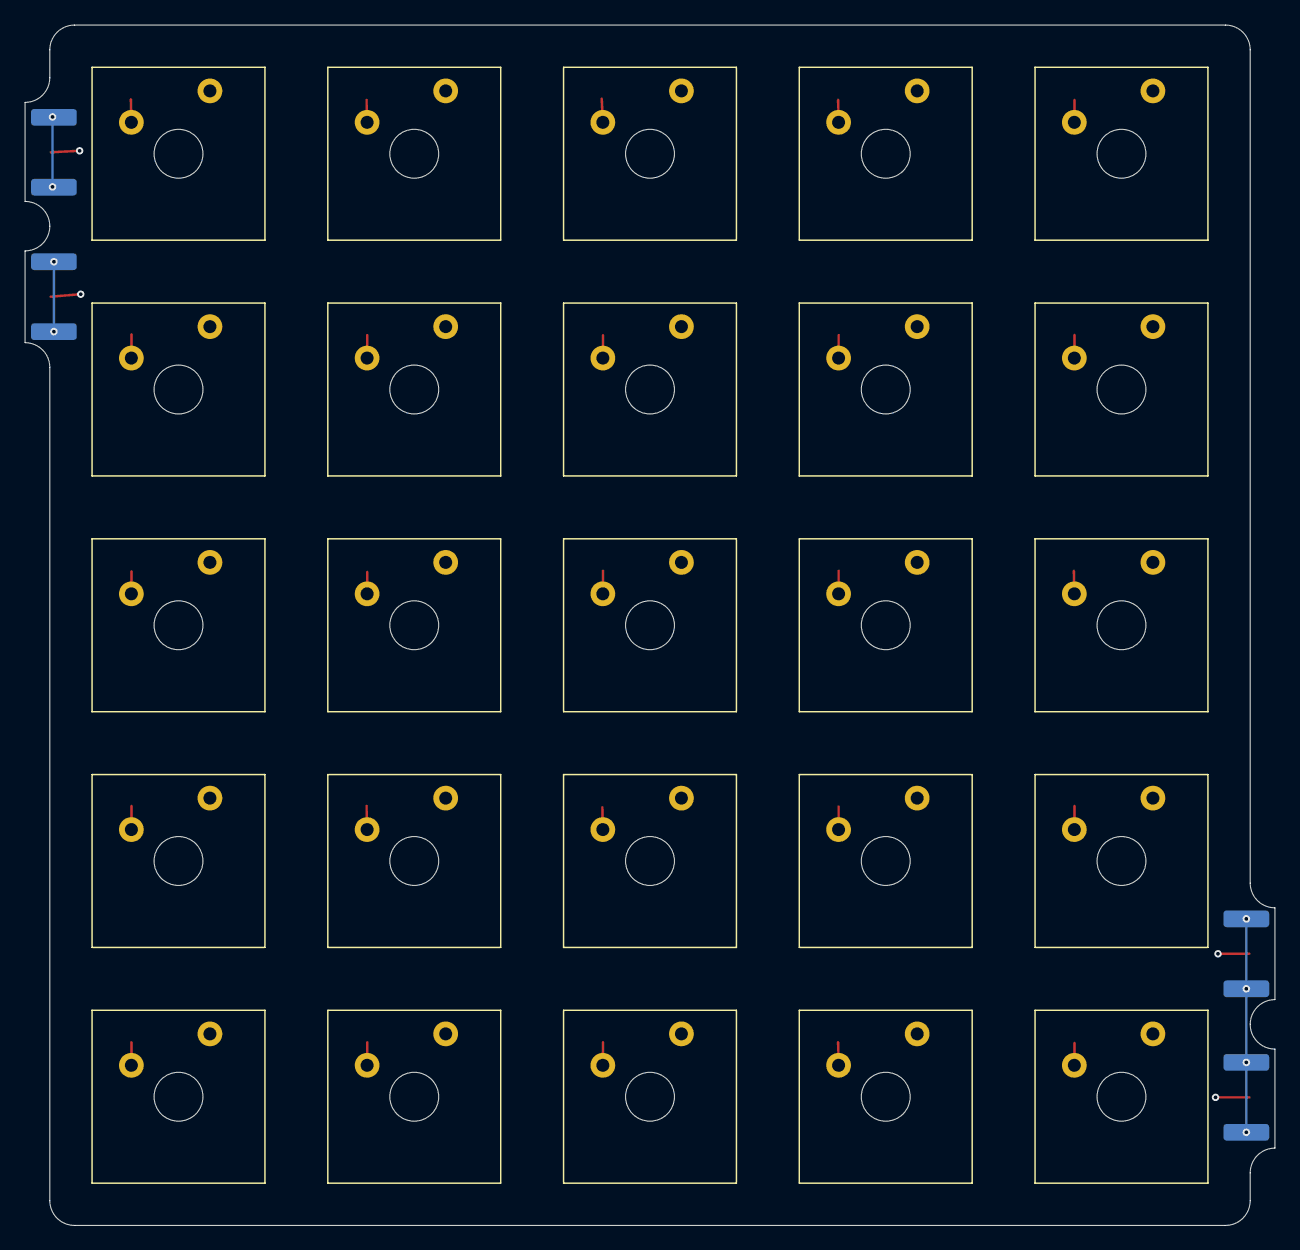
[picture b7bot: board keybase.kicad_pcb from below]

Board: 4 copper layers, 101.0 x 97.0 mm, 54 parts (25 on the bottom side), 28 nets.
